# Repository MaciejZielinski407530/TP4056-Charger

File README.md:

# TP4056-Charger

Projekt układu ładowania dla pojedynczego akumulatora 3,7V. 

Schemat układ opiera się na dostępych ładowarkach wykorzystujących układ TP4056.

Projekt polegał na wymianie zasilania w czołowej lampce LED z bateryjnego na akumulatorowe.
W tym celu należało zmodyfikować kształt PCB układu, aby dopasować go do lampki.

Dodatkowo utworzono footprinty dla układów TP4056 oraz 8205A.

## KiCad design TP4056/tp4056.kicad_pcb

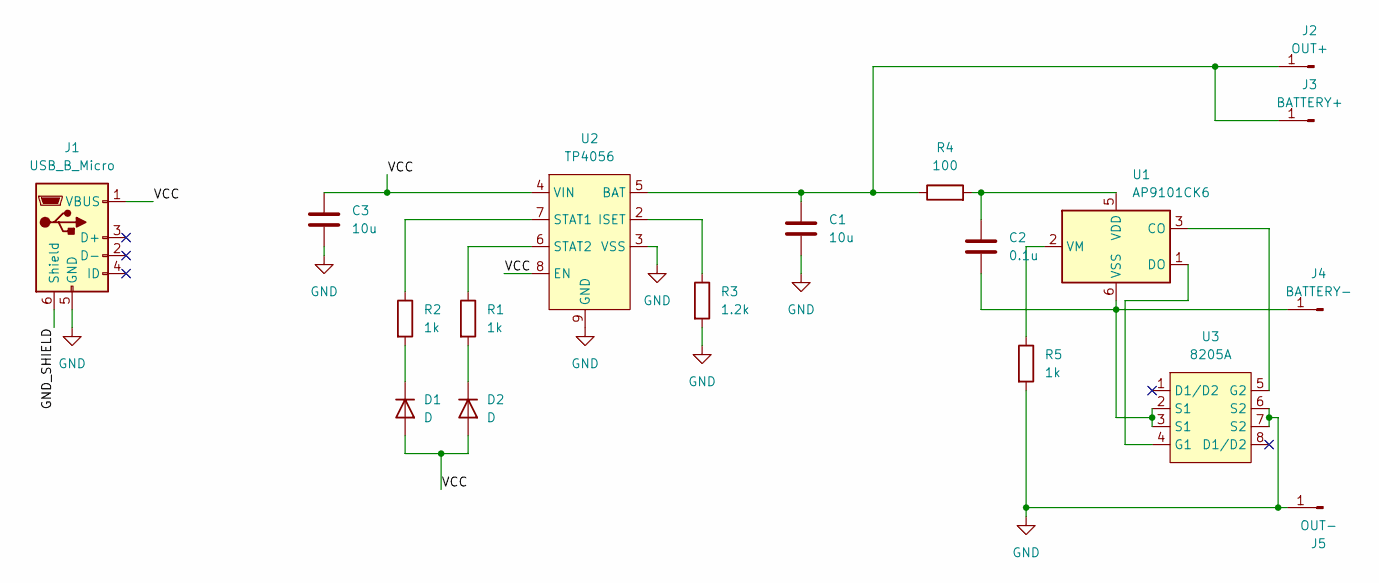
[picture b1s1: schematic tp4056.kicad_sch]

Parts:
C1: 10u; C_0603_1608Metric_Pad1.08x0.95mm_HandSolder
C2: 0.1u; C_0402_1005Metric_Pad0.74x0.62mm_HandSolder
C3: 10u; C_0402_1005Metric_Pad0.74x0.62mm_HandSolder
D1, D2: D; D_0805_2012Metric_Pad1.15x1.40mm_HandSolder
J1: USB_B_Micro; USB_Micro-B_Amphenol_10104110_Horizontal
J2: OUT+; SolderWire-0.5sqmm_1x01_D0.9mm_OD2.1mm
J3: BATTERY+; SolderWire-0.5sqmm_1x01_D0.9mm_OD2.1mm
J4: BATTERY-; SolderWire-0.5sqmm_1x01_D0.9mm_OD2.1mm
J5: OUT-; SolderWire-0.5sqmm_1x01_D0.9mm_OD2.1mm
R1, R2, R5: 1k; R_0603_1608Metric_Pad0.98x0.95mm_HandSolder
R3: 1.2k; R_0603_1608Metric_Pad0.98x0.95mm_HandSolder
R4: 100; R_0603_1608Metric_Pad0.98x0.95mm_HandSolder
U1: AP9101CK6; SOT-23-6
U2: TP4056
U3: 8205A

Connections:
/GND_SHIELD: J1.6 (Shield)
/VCC: C3.1, D1.2 (A), D2.2 (A), J1.1 (VBUS), U2.4 (VIN), U2.8 (EN)
GND: C1.2, C3.2, J1.5 (GND), J5.1, R3.2, R5.2, U2.3 (VSS), U2.9 (GND), U3.6 (S2), U3.7 (S2)
unnamed: D1.1 (K), R2.2
unnamed: D2.1 (K), R1.2
unnamed: C1.1, J2.1, J3.1, R4.1, U2.5 (BAT)
unnamed: C2.2, J4.1, U1.6 (VSS), U3.2 (S1), U3.3 (S1)
unnamed: U1.3 (CO), U3.5 (G2)
unnamed: U1.1 (DO), U3.4 (G1)
unnamed: C2.1, R4.2, U1.5 (VDD)
unnamed: R5.1, U1.2 (VM)
unnamed: R3.1, U2.2 (ISET)
unnamed: R2.1, U2.7 (STAT1)
unnamed: R1.1, U2.6 (STAT2)

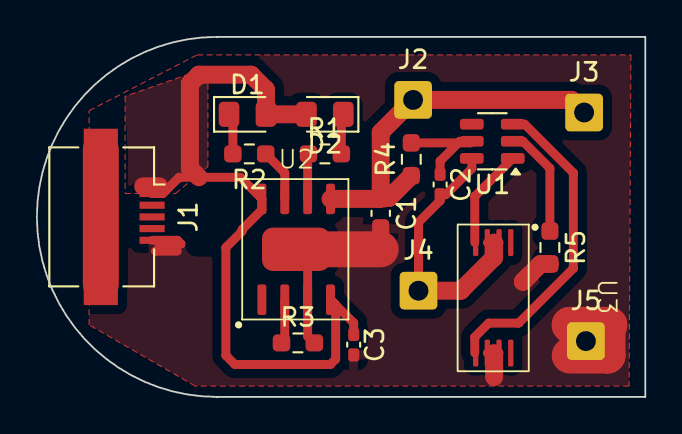
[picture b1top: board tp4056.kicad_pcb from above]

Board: 2 copper layers, 33.8 x 20.0 mm, 18 parts (0 on the bottom side), 13 nets.
